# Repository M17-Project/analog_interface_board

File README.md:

# analog_interface_board
USB analog interface board (a soundcard) built around C-Media CM6206 chip. Requires a 10 MHz reference. Can be used to handle M17 baseband.

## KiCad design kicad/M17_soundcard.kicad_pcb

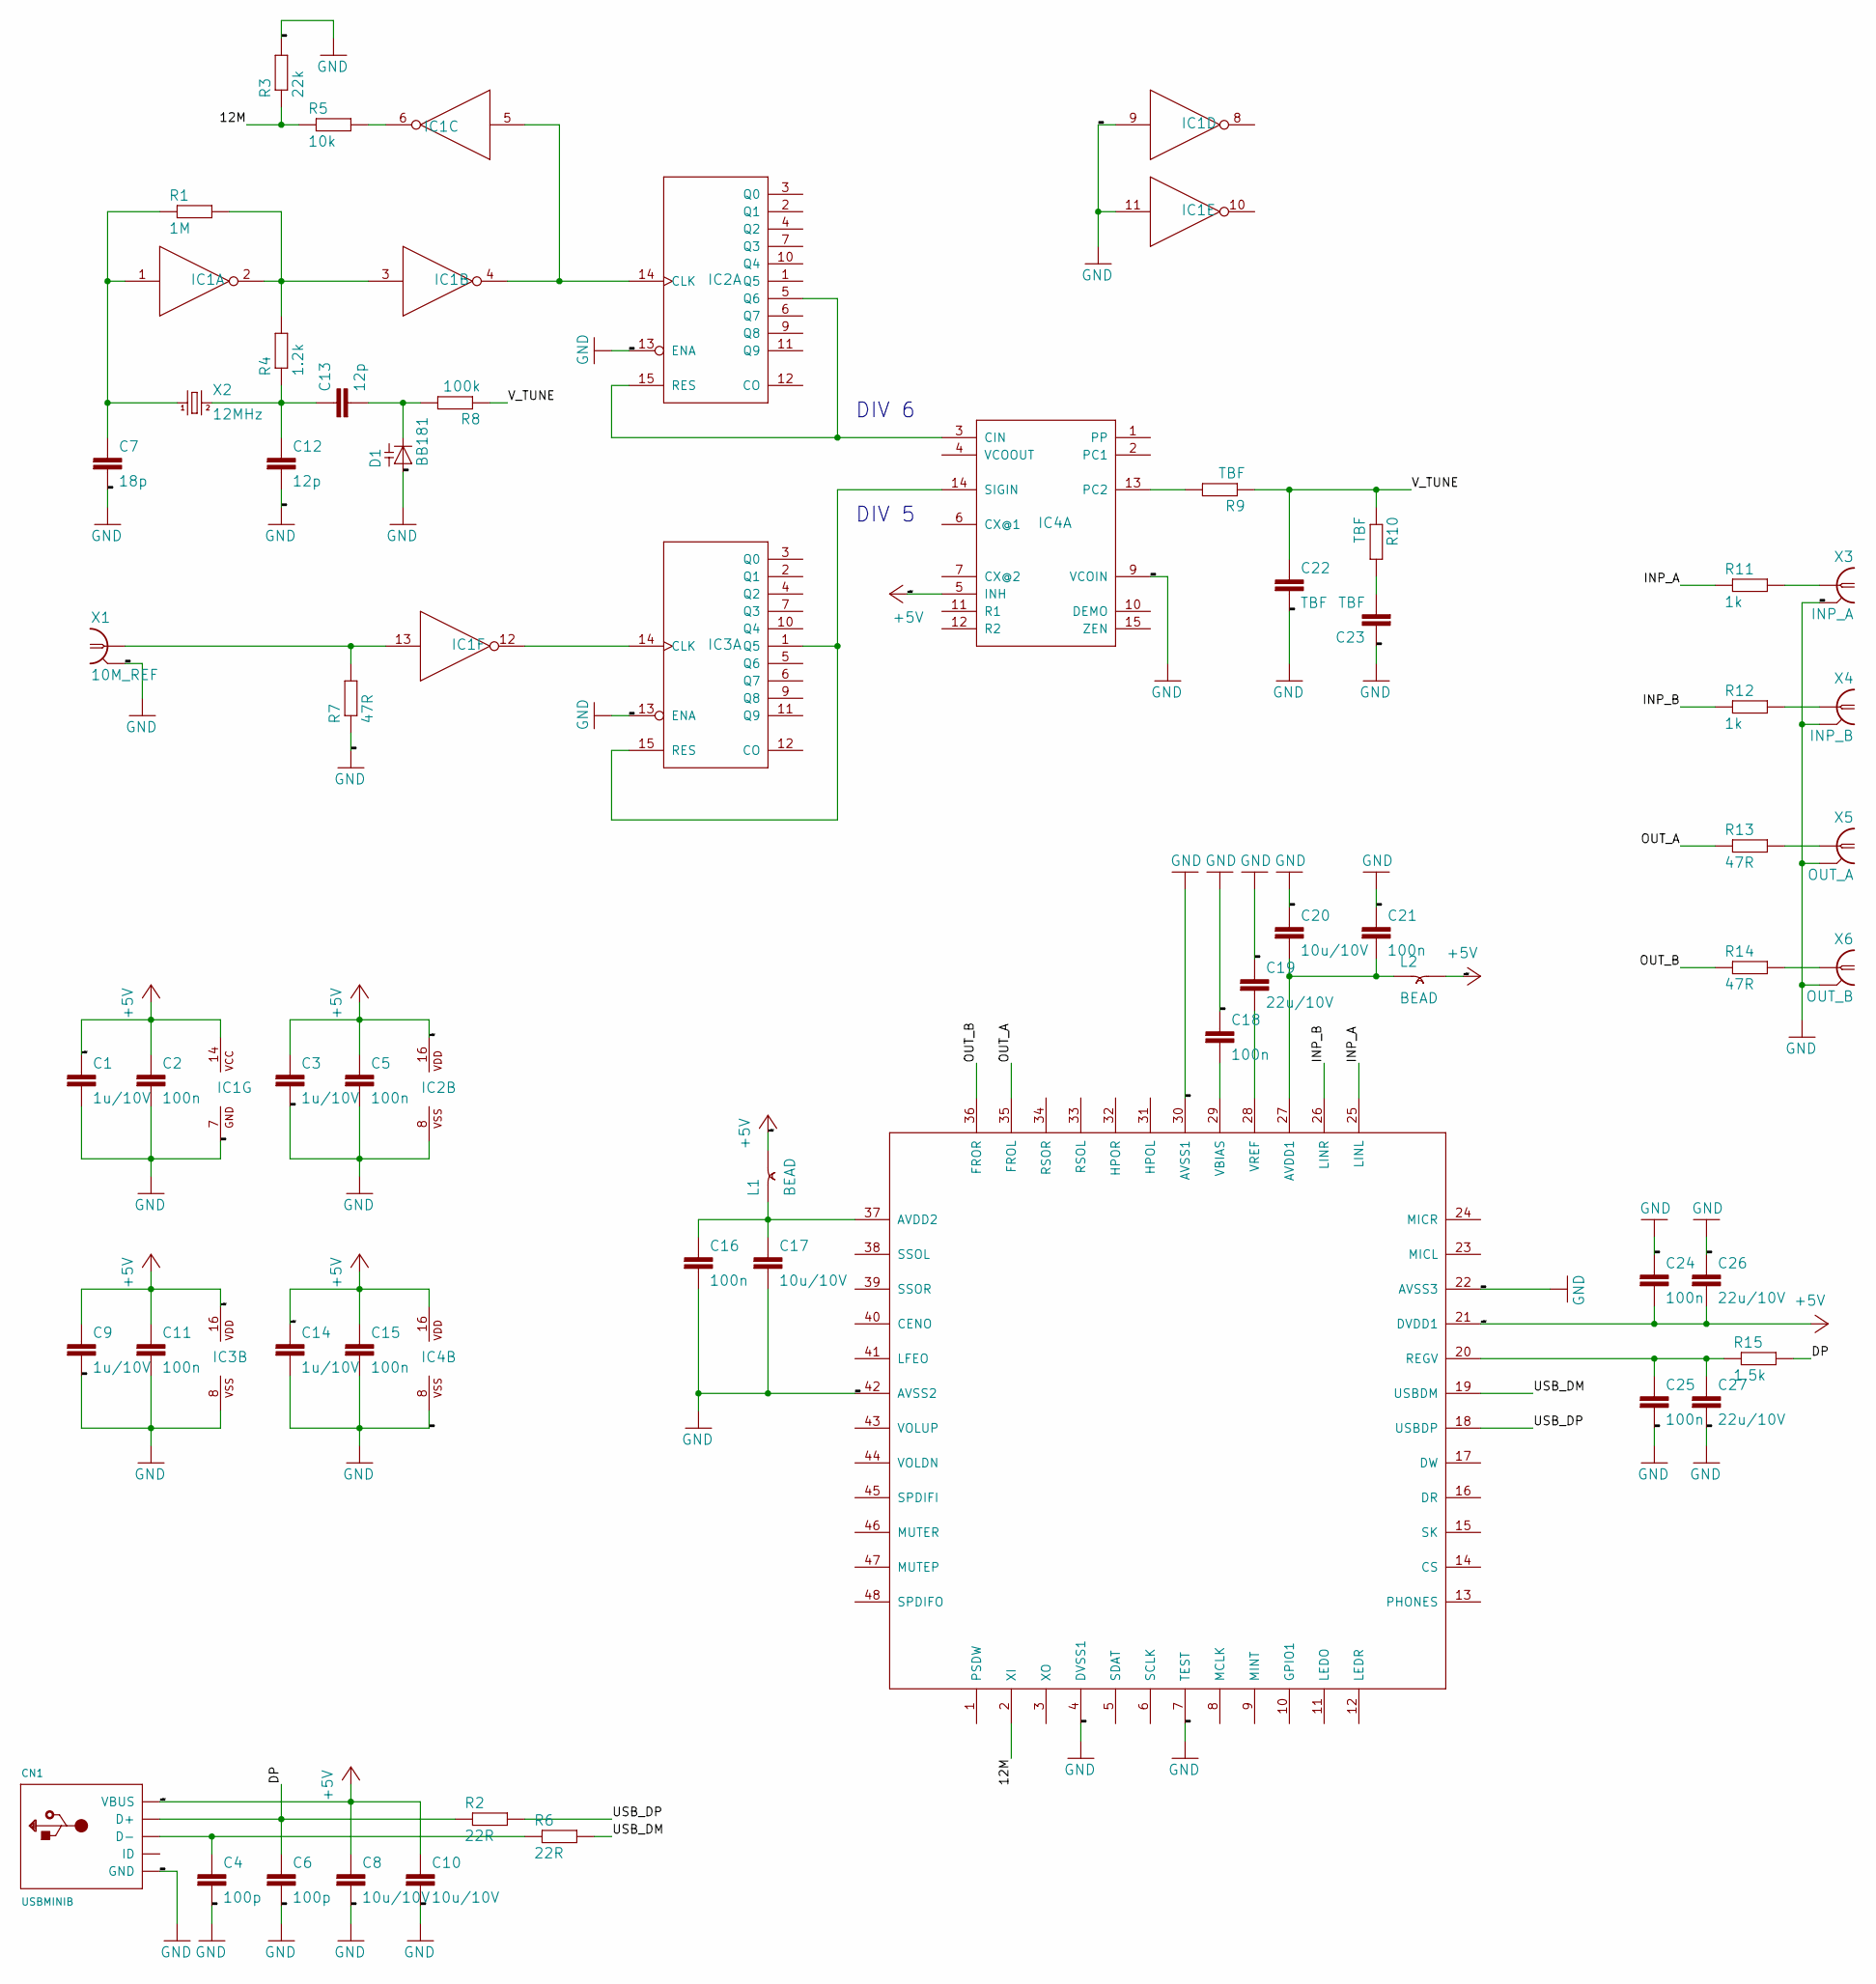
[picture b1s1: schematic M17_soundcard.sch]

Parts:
C1, C3, C9, C14: 1u/10V; C0805
C2, C5, C11, C15, C16, C18, C21, C24, C25: 100n; C0805
C4, C6: 100p; C0805
C7: 18p; C0805
C8, C10: 10u/10V; C1206
C12, C13: 12p; C0805
C17, C20: 10u/10V; C0805
C19, C26, C27: 22u/10V; C0805
C22, C23: TBF; C0805
CN1: USBMINIB; USB-MINIB
D1: BB181; SOD523
IC1: 7404D; SO14
IC2, IC3: 74HCT4017D; SO16
IC4: 74HCT4046D; SO16
L1, L2: BEAD; SM-B5
R1: 1M; R0805
R2, R6: 22R; R0805
R3: 22k; R0805
R4: 1.2k; R0805
R5: 10k; R0805
R7, R13, R14: 47R; R0805
R8: 100k; R0805
R9, R10: TBF; R0805
R11, R12: 1k; R0805
R15: 1.5k; R0805
U1: CM6206; LQFP-48
X1: 10M_REF; AMP_227161
X2: 12MHz; HC49
X3: INP_A; AMP_227161
X4: INP_B; AMP_227161
X5: OUT_A; AMP_227161
X6: OUT_B; AMP_227161

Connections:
12M: R3.1, R5.1, U1.2 (XI)
+5V: C1.1, C2.1, C3.1, C5.1, C8.1, C9.1, C10.1, C11.1, C14.1, C15.1, C24.2, C26.2, CN1.VBUS, IC1.14 (VCC), IC2.16 (VDD), IC3.16 (VDD), IC4.5 (INH), IC4.16 (VDD), L1.2, L2.2, U1.21 (DVDD1)
DP: C6.1, CN1.D+, R2.1, R15.2
GND: C1.2, C2.2, C3.2, C4.2, C5.2, C6.2, C7.2, C8.2, C9.2, C10.2, C11.2, C12.2, C14.2, C15.2, C16.2, C17.2, C18.1, C19.1, C20.1, C21.1, C22.2, C23.1, C24.1, C25.2, C26.1, C27.2, CN1.GND, CN1.GND1, CN1.GND2, CN1.GND3, CN1.GND4, D1.A, IC1.7 (GND), IC1.9 (I), IC1.11 (I), IC2.8 (VSS), IC2.13 (ENA), IC3.8 (VSS), IC3.13 (ENA), IC4.8 (VSS), IC4.9 (VCOIN), R3.2, R7.1, U1.4 (DVSS1), U1.7 (TEST), U1.22 (AVSS3), U1.30 (AVSS1), U1.42 (AVSS2), X1.2, X3.2, X4.2, X5.2, X6.2
INP_A: R11.1, U1.25 (LINL)
INP_B: R12.1, U1.26 (LINR)
unnamed: C4.1, CN1.D-, R6.1
unnamed: IC3.1 (Q5), IC3.15 (RES), IC4.14 (SIGIN)
unnamed: R13.2, X5.1
unnamed: R14.2, X6.1
unnamed: R12.2, X4.1
unnamed: R11.2, X3.1
unnamed: C16.1, C17.1, L1.1, U1.37 (AVDD2)
unnamed: C7.1, IC1.1 (I), R1.1, X2.1
unnamed: IC1.13 (I), R7.2, X1.1
unnamed: IC2.5 (Q6), IC2.15 (RES), IC4.3 (CIN)
unnamed: C18.2, U1.29 (VBIAS)
unnamed: C19.2, U1.28 (VREF)
unnamed: C12.1, C13.1, R4.1, X2.2
unnamed: IC1.2 (O), IC1.3 (I), R1.2, R4.2
unnamed: C13.2, D1.C, R8.2
unnamed: IC1.4 (O), IC1.5 (I), IC2.14 (CLK)
unnamed: IC1.12 (O), IC3.14 (CLK)
unnamed: IC4.13 (PC2), R9.2
unnamed: C20.2, C21.2, L2.1, U1.27 (AVDD1)
unnamed: C23.2, R10.2
unnamed: IC1.6 (O), R5.2
unnamed: C25.1, C27.1, R15.1, U1.20 (REGV)
OUT_A: R13.1, U1.35 (FROL)
OUT_B: R14.1, U1.36 (FROR)
USB_DM: R6.2, U1.19 (USBDM)
USB_DP: R2.2, U1.18 (USBDP)
V_TUNE: C22.1, R8.1, R9.1, R10.1

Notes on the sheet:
DIV 6
DIV 5

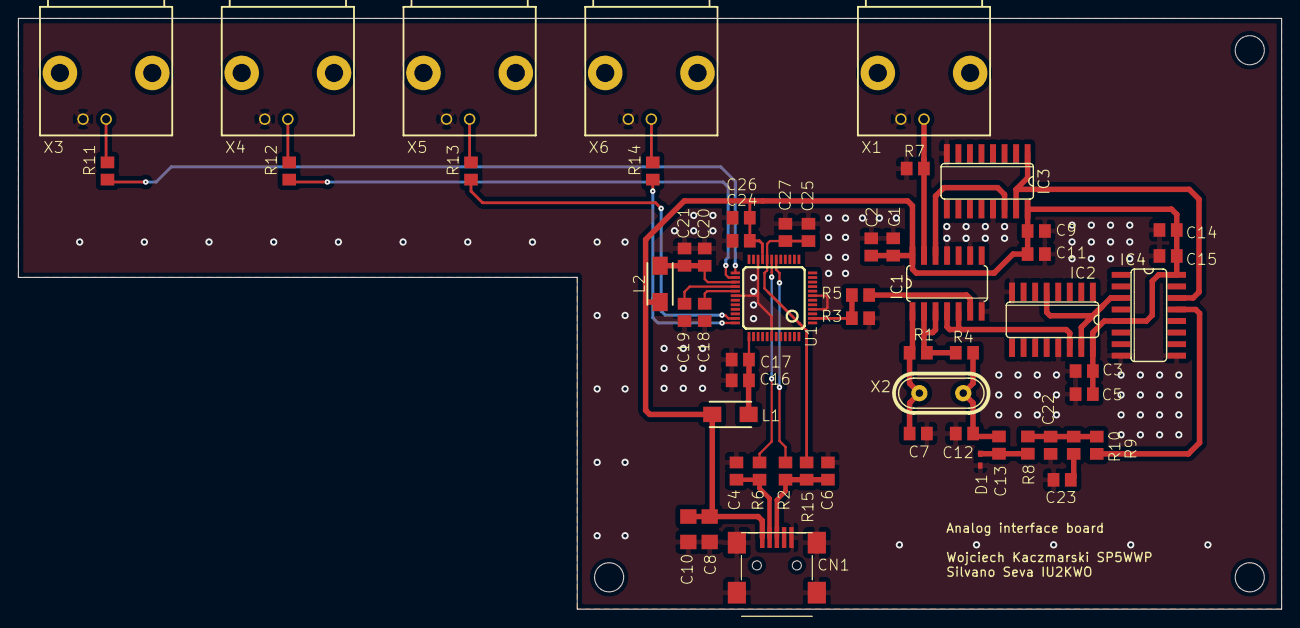
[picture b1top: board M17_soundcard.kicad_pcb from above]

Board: 2 copper layers, 139.0 x 65.0 mm, 60 parts (0 on the bottom side), 33 nets.

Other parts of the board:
 : MountingHole_3.2mm_M3_ISO7380
 #2,  #3: MountingHole_3.2mm_M3_ISO7380

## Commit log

2021-05-11 Changed board shape, added GND connections to USB socket, added PDF file with schematic
2021-05-11 Updated gerber files
2021-05-19 Updated the values of some components, re-generated the schematic PDF file
2021-10-29 Changed value of R10 too 100 ohm
2022-01-15 Update components' values for PLL filter
